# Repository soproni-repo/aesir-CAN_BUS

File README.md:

Find "KiCad" folder on your pc. (for me it was in \documents\KiCad)
Make a new folder inside "KiCad" called "CAN_BUS"
Import everything here to "CAN_BUS"

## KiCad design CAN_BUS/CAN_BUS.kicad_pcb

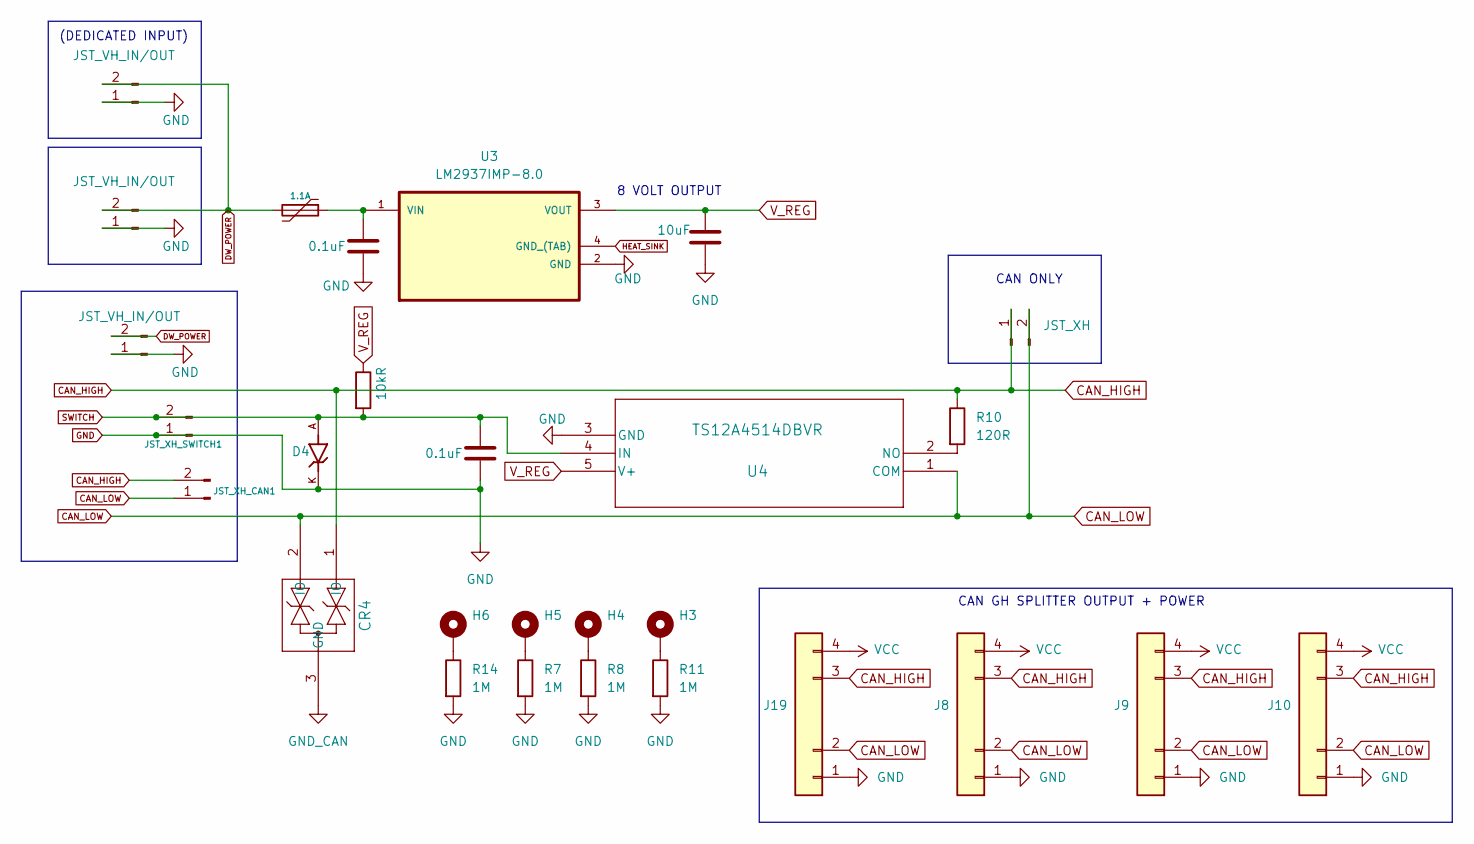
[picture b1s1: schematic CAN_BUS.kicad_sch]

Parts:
C3, C4: 0.1uF; C_0805_2012Metric_Pad1.18x1.45mm_HandSolder
C5: 10uF; C_0805_2012Metric_Pad1.18x1.45mm_HandSolder
CR4: ESD2CAN36DBZRQ1; SOT-23-3_DBZ_TEX
D4: UCLAMP1071P.TNT; DIO_UCLAMP1071P.TNT; PARTREV 8.1
F1: 1.1A; Fuse_1812_4532Metric_Pad1.30x3.40mm_HandSolder
H3, H4, H5, H6: MountingHole_Pad; MountingHole_3.2mm_M3_Pad_Via
J6, J11, J17: JST_VH_IN/OUT; JST_VH_B2P-VH-FB-B_1x02_P3.96mm_Vertical
J8, J9, J10, J19: Conn_01x04; JST_GH_BM04B-GHS-TBT_1x04-1MP_P1.25mm_Vertical
J16: JST_XH; JST_XH_B2B-XH-A_1x02_P2.50mm_Vertical
JST_XH_CAN1: JST XH B2B-XH-A; JST_XH_B2B-XH-A_1x02_P2.50mm_Vertical
JST_XH_SWITCH1: JST XH B2B-XH-A; JST_XH_B2B-XH-A_1x02_P2.50mm_Vertical
R7, R8, R11, R14: 1M; R_0805_2012Metric_Pad1.20x1.40mm_HandSolder
R9: 10kR; R_0805_2012Metric_Pad1.20x1.40mm_HandSolder
R10: 120R; R_0805_2012Metric_Pad1.20x1.40mm_HandSolder
U3: LM2937IMP-8.0; SOT230P700X180-4N
U4: TS12A4514DBVR; DBV5

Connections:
CAN_HIGH: CR4.1 (IO), J8.3, J9.3, J10.3, J16.1, J19.3, JST_XH_CAN1.2, R10.1
CAN_LOW: CR4.2 (IO), J8.2, J9.2, J10.2, J16.2, J19.2, JST_XH_CAN1.1, U4.1 (COM)
DW_POWER: F1.2, J6.2, J11.2, J17.2
GND: C3.1, C4.1, C5.1, D4.K, J6.1, J8.1, J9.1, J10.1, J11.1, J17.1, J19.1, JST_XH_SWITCH1.1, R7.2, R8.2, R11.2, R14.2, U3.2 (GND), U4.3 (GND)
GND_CAN: CR4.3 (GND)
HEAT_SINK: U3.4 (GND_(TAB))
unnamed: H3.1, R11.1
unnamed: H4.1, R8.1
unnamed: H5.1, R7.1
unnamed: H6.1, R14.1
unnamed: C3.2, F1.1, U3.1 (VIN)
unnamed: R10.2, U4.2 (NO)
SWITCH: C4.2, D4.A, JST_XH_SWITCH1.2, R9.2, U4.4 (IN)
VCC: J8.4, J9.4, J10.4, J19.4
V_REG: C5.2, R9.1, U3.3 (VOUT), U4.5 (V+)

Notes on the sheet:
CAN GH SPLITTER OUTPUT + POWER
8 VOLT OUTPUT
(DEDICATED INPUT)
CAN ONLY

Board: 2 copper layers, 28 parts (0 on the bottom side), 13 nets, no tracks yet.

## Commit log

2024-11-07 Create CAN_BUS
